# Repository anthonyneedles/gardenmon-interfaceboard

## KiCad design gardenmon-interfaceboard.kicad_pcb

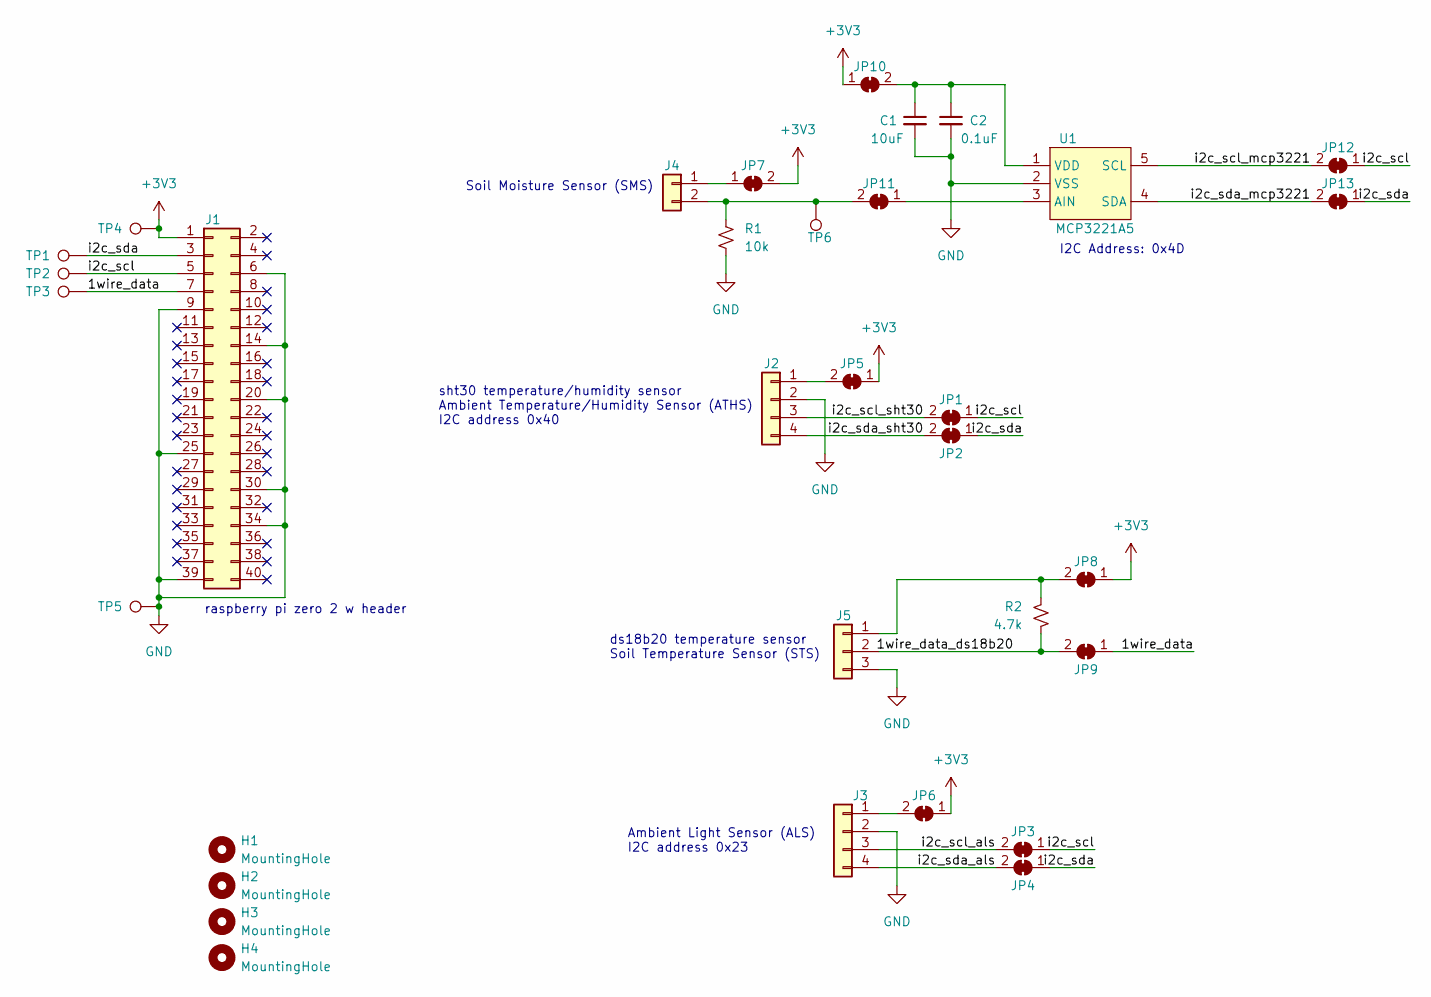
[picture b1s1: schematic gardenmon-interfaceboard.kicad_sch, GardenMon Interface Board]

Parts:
C1: 10uF; C_0603_1608Metric_Pad1.08x0.95mm_HandSolder; Part Number CL10A106KQ8NNNC
C2: 0.1uF; C_0603_1608Metric_Pad1.08x0.95mm_HandSolder; Part Number CL10B104KB8NNWC
H1, H2, H3, H4: MountingHole; MountingHole_2.7mm_M2.5
J1: Conn_02x20_Odd_Even; PinHeader_2x20_P2.54mm_Vertical
J2, J3: Conn_01x04; JST_PH_S4B-PH-K_1x04_P2.00mm_Horizontal; Part Number S4B-PH-K-S
J4: Conn_01x02; JST_PH_S2B-PH-K_1x02_P2.00mm_Horizontal; Part Number S2B-PH-K-S
J5: Conn_01x03; JST_PH_S3B-PH-K_1x03_P2.00mm_Horizontal; Part Number S3B-PH-K-S
JP1, JP2, JP3, JP4, JP5, JP6, JP7, JP8, JP9, JP10, JP11, JP12, JP13: SolderJumper_2_Bridged; SolderJumper-2_P1.3mm_Open_TrianglePad1.0x1.5mm
R1: 10k; R_0603_1608Metric_Pad0.98x0.95mm_HandSolder; Part Number RC0603FR-0710KL
R2: 4.7k; R_0603_1608Metric_Pad0.98x0.95mm_HandSolder; Part Number RC0603FR-074K7L
TP1, TP2, TP3, TP4, TP5, TP6: TestPoint; TestPoint_THTPad_2.5x2.5mm_Drill1.2mm
U1: MCP3221A5; SOT-23-5_HandSoldering; Part Number MCP3221A5T-E/OT

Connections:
+3V3: J1.1, JP5.1 (A), JP6.1 (A), JP7.2 (B), JP8.1 (A), JP10.1 (A), TP4.1
/1wire_data: J1.7, JP9.1 (A), TP3.1
/1wire_data_ds18b20: J5.2, JP9.2 (B), R2.2
/i2c_scl: J1.5, JP1.1 (A), JP3.1 (A), JP12.1 (A), TP2.1
/i2c_scl_als: J3.3, JP3.2 (B)
/i2c_scl_mcp3221: JP12.2 (B), U1.5 (SCL)
/i2c_scl_sht30: J2.3, JP1.2 (B)
/i2c_sda: J1.3, JP2.1 (A), JP4.1 (A), JP13.1 (A), TP1.1
/i2c_sda_als: J3.4, JP4.2 (B)
/i2c_sda_mcp3221: JP13.2 (B), U1.4 (SDA)
/i2c_sda_sht30: J2.4, JP2.2 (B)
GND: C1.2, C2.2, J1.6, J1.9, J1.14, J1.20, J1.25, J1.30, J1.34, J1.39, J2.2, J3.2, J5.3, R1.2, TP5.1, U1.2 (VSS)
unnamed: J2.1, JP5.2 (B)
unnamed: J3.1, JP6.2 (B)
unnamed: J4.1, JP7.1 (A)
unnamed: J4.2, JP11.2 (B), R1.1, TP6.1
unnamed: J5.1, JP8.2 (B), R2.1
unnamed: C1.1, C2.1, JP10.2 (B), U1.1 (VDD)
unnamed: JP11.1 (A), U1.3 (AIN)

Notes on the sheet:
ds18b20 temperature sensor Soil Temperature Sensor (STS)
raspberry pi zero 2 w header
I2C Address: 0x4D
Ambient Light Sensor (ALS) I2C address 0x23
sht30 temperature/humidity sensor Ambient Temperature/Humidity Sensor (ATHS) I2C address 0x40
Soil Moisture Sensor (SMS)

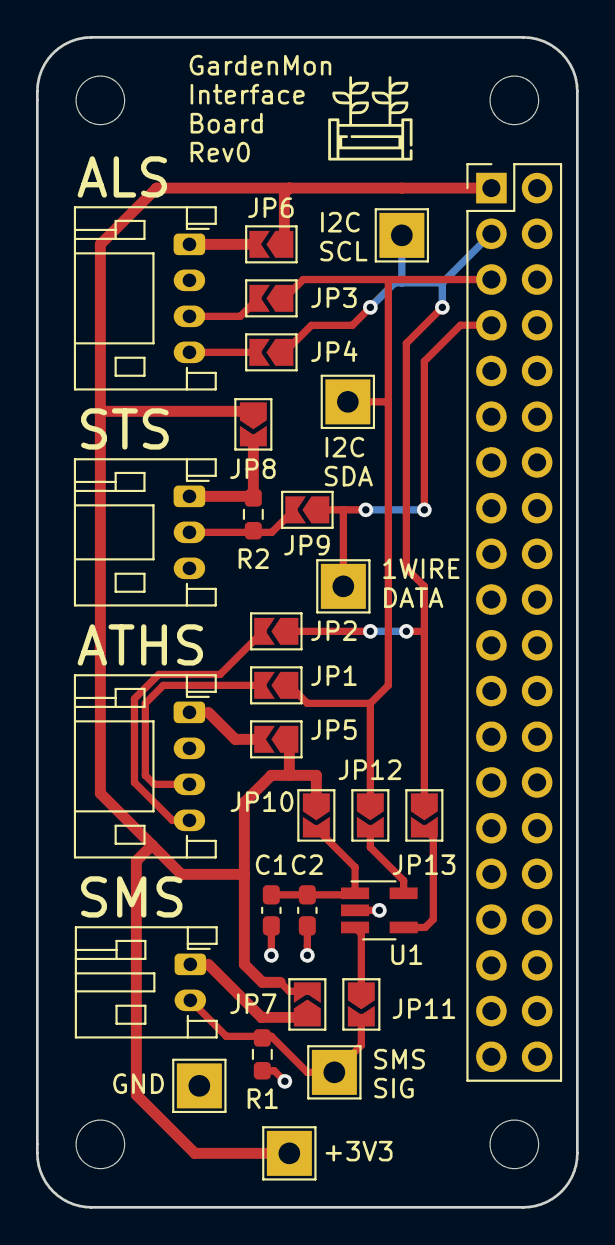
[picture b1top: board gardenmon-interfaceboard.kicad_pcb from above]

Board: 2 copper layers, 30.0 x 65.0 mm, 33 parts (0 on the bottom side), 19 nets.

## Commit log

2024-02-19 init:
2024-02-19 sch: add all connections
2024-02-19 sch/pcb: add footprints, setup PCBNew for OSHPark
2024-02-19 pcb: add footprints, board layout
2024-02-19 temp:
2024-02-20 rev0: release of rev0
